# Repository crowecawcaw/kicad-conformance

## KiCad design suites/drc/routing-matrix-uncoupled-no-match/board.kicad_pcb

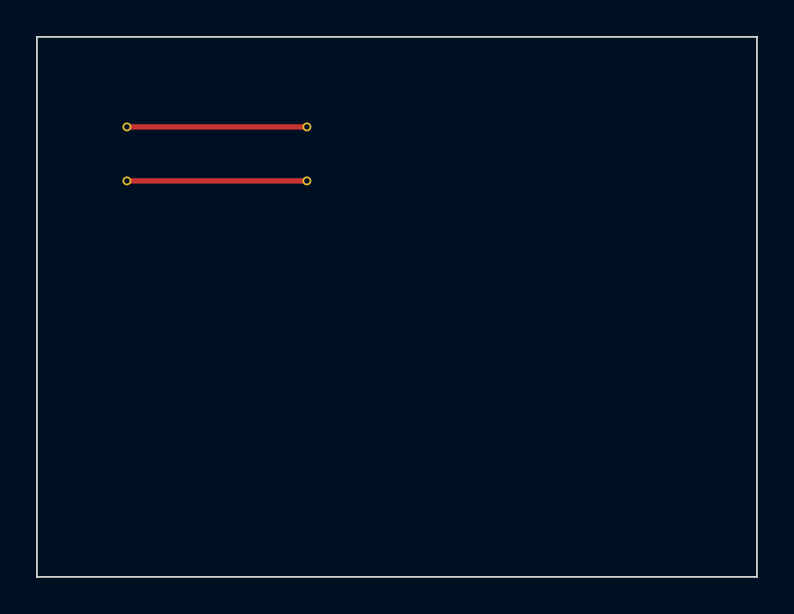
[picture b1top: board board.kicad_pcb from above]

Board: 2 copper layers, 40.0 x 30.0 mm, 4 parts (0 on the bottom side), 2 nets.

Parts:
PAIR_NA: TestPad
PAIR_NB: TestPad
PAIR_PA: TestPad
PAIR_PB: TestPad

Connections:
PAIR_N: PAIR_NA.1, PAIR_NB.1
PAIR_P: PAIR_PA.1, PAIR_PB.1
